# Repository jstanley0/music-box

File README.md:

# music-box
Chiptune music player featuring SN76489 and ATtiny861/ATtiny84

## Overview
This project grew out of a Wikipedia surfing session. In reading about the computers of my childhood,
I came across an article about the TI SN76489 sound chip, used by two of the machines I used as a kid
(the TI 99/4A and IBM PCjr). I wondered if you can readily buy this IC, and if you can talk to it
reasonably easily with modern hardware. The answer to both questions is yes!

## How it works
All eight pins of PORTA are connected to the SN76489's data lines. PB4 connects to /WE and latches
a value to the chip. PB5 (CLKO) outputs the ATtiny861's clock signal directly to the sound chip's
clock input. /OE is permanently tied low and READY is ignored. I'm not sharing a bus with anything 
else...

The MCU firmware plays music from an array of bytes stored in program memory (in songs.c). It's a
very simple binary format with three one-byte commands that play a note, play a noise, and sleep.
To keep things simple, I ignore note-off events and simply make each note decay at a constant
linear rate after it is struck. Much like an actual music box!

## Loading music
util/process_midi_file.cpp will take a MIDI file and output a set of arrays for songs.c. It makes
use of [light-midi-parser](https://github.com/imhcyx/light-midi-parser) as a submodule.

## ATtiny84
This project can also be built for the ATtiny84, via `make -e DEVICE=attiny84`.
With this target there will be just one blinking light, rather than one per channel. See main.c for wiring differences.

## See also
I've also created a more elaborate stereo two-chip player using the Raspberry Pi Pico, [pico-player](https://github.com/jstanley0/pico-player).

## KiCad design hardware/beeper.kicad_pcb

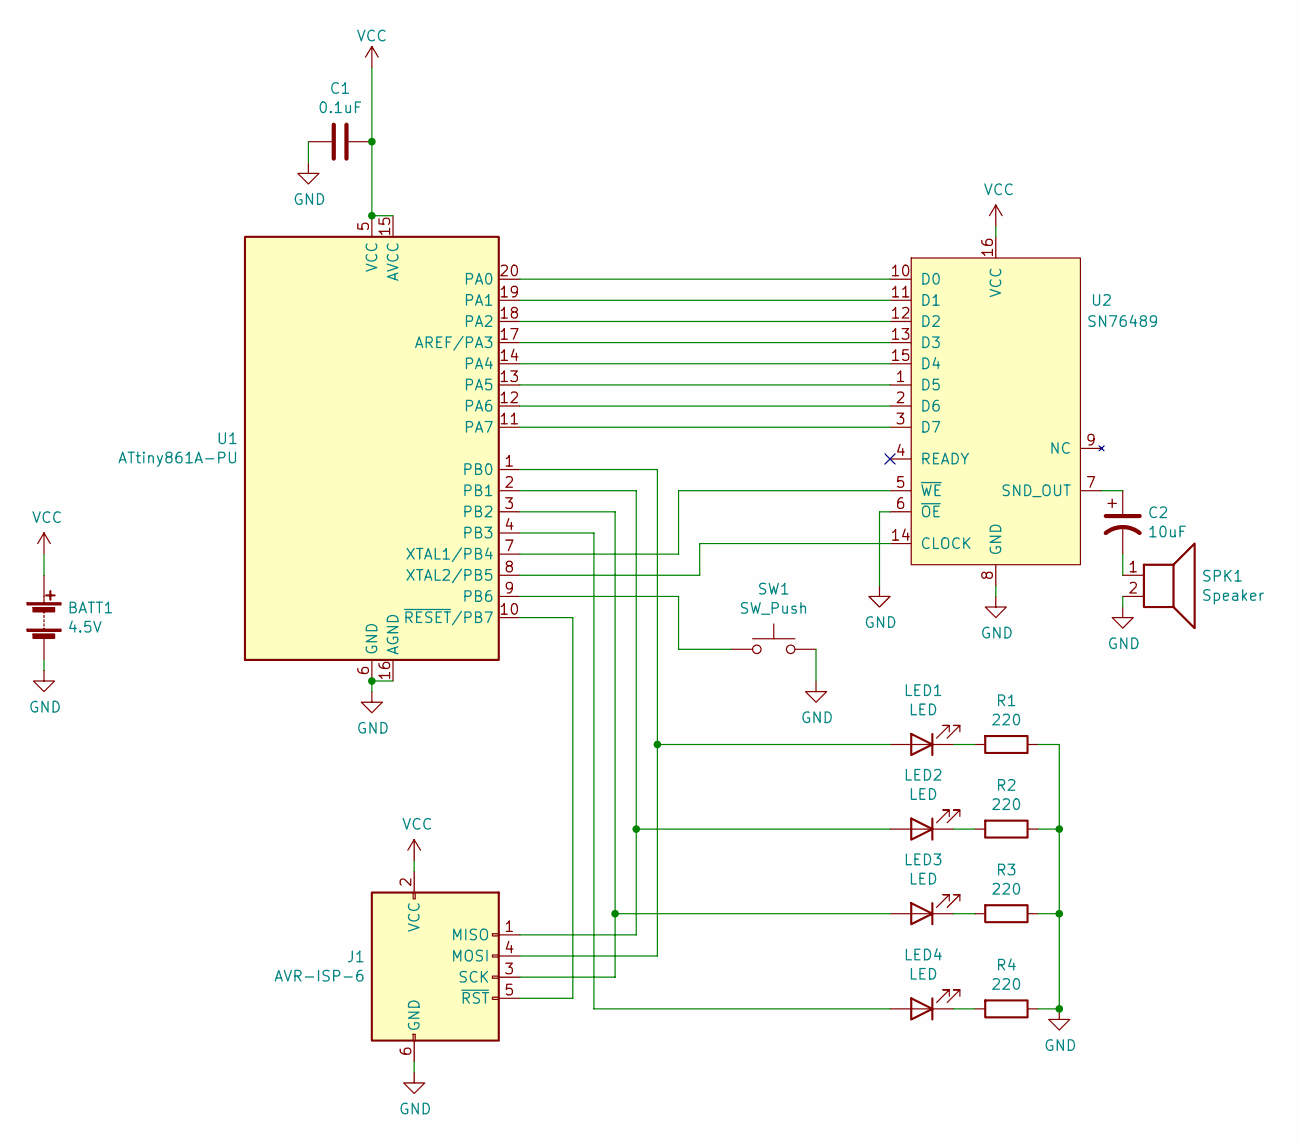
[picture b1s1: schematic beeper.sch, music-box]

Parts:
BATT1: 4.5V; PinHeader_1x02_P2.54mm_Vertical
C1: 0.1uF; C_Disc_D3.0mm_W1.6mm_P2.50mm
C2: 10uF; CP_Radial_D6.3mm_P2.50mm
J1: AVR-ISP-6; PinHeader_2x03_P2.54mm_Vertical
LED1, LED2, LED3, LED4: LED; LED_D5.0mm_Clear
R1, R2, R3, R4: 220; R_Axial_DIN0204_L3.6mm_D1.6mm_P1.90mm_Vertical
SPK1: Speaker; PinHeader_1x02_P2.54mm_Vertical
SW1: SW_Push; SW_Tactile_Straight_KSA0Axx1LFTR
U1: ATtiny861A-PU; DIP-20_W7.62mm
U2: SN76489; DIP-16_W7.62mm

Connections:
GND: BATT1.2 (-), C1.2, J1.6 (GND), R1.1, R2.1, R3.1, R4.1, SPK1.2, SW1.2, U1.6 (GND), U1.16 (AGND), U2.6 (~OE), U2.8 (GND)
unnamed: C2.1, U2.7 (SND_OUT)
unnamed: C2.2, SPK1.1
unnamed: J1.1 (MISO), LED2.2 (A), U1.2 (PB1)
unnamed: J1.3 (SCK), LED3.2 (A), U1.3 (PB2)
unnamed: J1.4 (MOSI), LED1.2 (A), U1.1 (PB0)
unnamed: J1.5 (~RST), U1.10 (~RESET~/PB7)
unnamed: LED1.1 (K), R1.2
unnamed: LED2.1 (K), R2.2
unnamed: LED3.1 (K), R3.2
unnamed: LED4.1 (K), R4.2
unnamed: LED4.2 (A), U1.4 (PB3)
unnamed: SW1.1, U1.9 (PB6)
unnamed: U1.7 (XTAL1/PB4), U2.5 (~WE)
unnamed: U1.8 (XTAL2/PB5), U2.14 (CLOCK)
unnamed: U1.11 (PA7), U2.3 (D7)
unnamed: U1.12 (PA6), U2.2 (D6)
unnamed: U1.13 (PA5), U2.1 (D5)
unnamed: U1.14 (PA4), U2.15 (D4)
unnamed: U1.17 (AREF/PA3), U2.13 (D3)
unnamed: U1.18 (PA2), U2.12 (D2)
unnamed: U1.19 (PA1), U2.11 (D1)
unnamed: U1.20 (PA0), U2.10 (D0)
VCC: BATT1.1 (+), C1.1, J1.2 (VCC), U1.5 (VCC), U1.15 (AVCC), U2.16 (VCC)

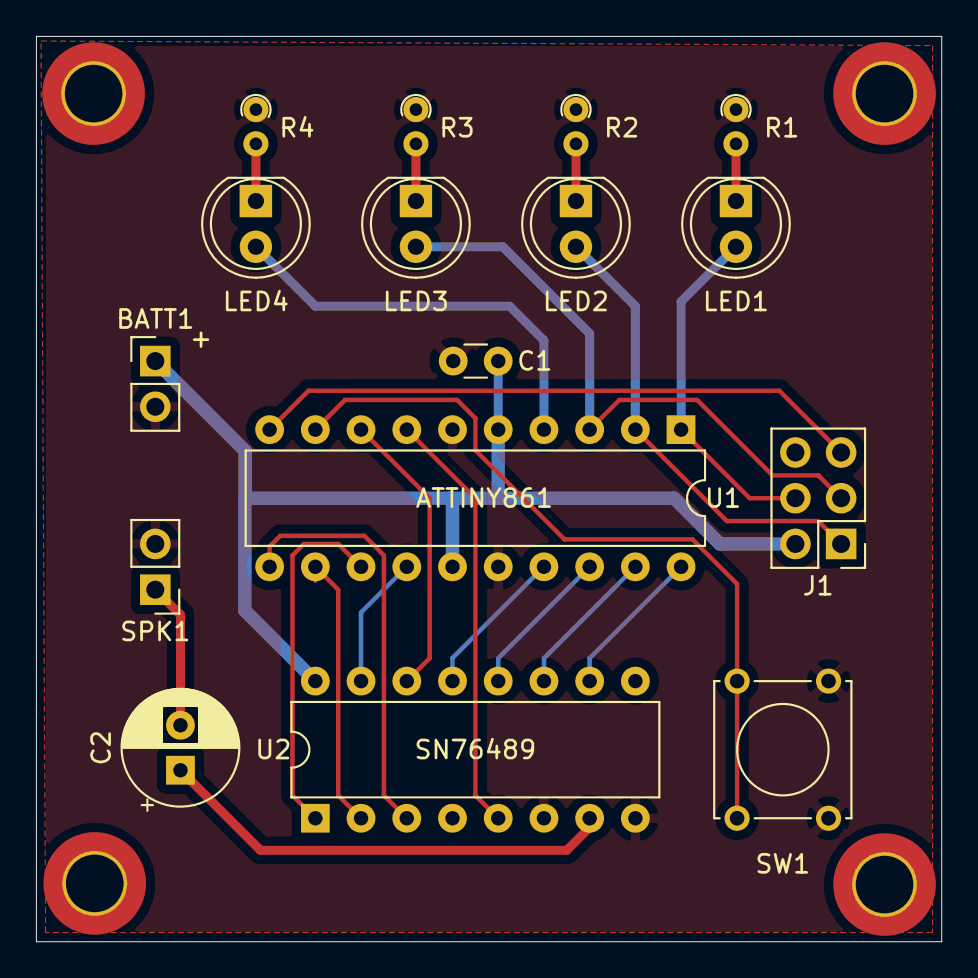
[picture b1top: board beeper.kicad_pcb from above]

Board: 2 copper layers, 50.3 x 50.3 mm, 17 parts (0 on the bottom side), 24 nets.

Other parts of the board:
\: MountingHole_3.2mm_M3_ISO7380_Pad_TopBottom

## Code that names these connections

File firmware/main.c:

// attiny861 / TI SN76489 music box
// (c) 2021 by Jeremy Stanley

// port assignments (ATtiny861 -> TI SN76489):
// PA0..PA7 -> D7..D0
// PB4 -> /WE
// PB5 -> CLOCK (via CKOUT fuse)

// other pin assignments:
// PB0..3 -> blinkenlights
// PB6 -> tac switch

// alternatively this can be compiled for ATtiny84
// using `make -e DEVICE=attiny84`
// which uses the following port assignments:
// PA0..PA7 -> D7..D0
// PB1 -> /WE
// PB2 -> CLOCK
// PB0 -> blinkenlight (just one)

#include <avr/io.h>
#include <avr/pgmspace.h>
#include <avr/sleep.h>
#include <avr/interrupt.h>
#include <util/delay.h>

#include "songs.h"
const uint8_t *const songs[] PROGMEM = { st_elsewhere, lament, macgyver, brooklet, quantum_leap, nervous, hogans_heroes, charlie_brown };
const uint8_t NUM_SONGS = sizeof(songs) / sizeof(songs[0]);

#ifdef __AVR_ATtiny84__
#define WE_BIT PORTB1
#else
#define WE_BIT PORTB4
#endif

// hi-hat, ride cymbal, etc. don't play at full volume
#define ATTENUATED_PERCUSSION_LEVEL 4

void init_clock()
{
  // change clock divider from /8 to /4 so we run at 2MHz,
  // which is an acceptable clock frequency for the SN76489
  // (at 4MHz, we lose too much low range, and at 1MHz, high notes get out of tune)
  CLKPR = (1 << CLKPCE);  // Clock Prescaler Change Enable - this part is necessary
  CLKPR = (1 << CLKPS1);  // 4x divider
}

void init_io()
{
  DDRA  = 0xff;
#ifdef __AVR_ATtiny84__
  DDRB  = 0b00000111;
  PORTB = (1 << WE_BIT);
#else
  DDRB  = 0b00111111;
  PORTB = (1 << PORTB6) | (1 << WE_BIT);
#endif
}

void send_byte(uint8_t byte)
{
  PORTA = byte;
  PORTB &= ~(1 << WE_BIT);
  _delay_us(16);  // 32 clock cycles at 2MHz
  PORTB |= (1 << WE_BIT);
}

void send_frequency(uint8_t voice, uint16_t freq)
{
  send_byte(0x80U | (voice << 5) | (freq & 0x0F));
  send_byte(freq >> 4);
}

void send_noise(uint8_t n)
{
  send_byte(0xE0U | n);
}

void send_attenuation(uint8_t voice, uint8_t atten)
{
  send_byte(0x90U | (voice << 5) | atten);
}

uint8_t playing_atten[4] = { 15, 15, 15, 15 };

#ifdef __AVR_ATtiny84__
volatile uint8_t OCR0A_buf = 0;

void update_blinkenlight()
{
  uint8_t blinkenlight = 0;
  for(uint8_t i = 0; i < 4; ++i) {
    blinkenlight += (63 >> playing_atten[i]);
  }
  OCR0A_buf = blinkenlight;
}
#else
static const uint8_t fade_table[16] PROGMEM = {254, 179, 125, 88, 61, 43, 30, 21, 15, 10, 7, 5, 4, 2, 1, 0};

volatile uint8_t OCR0A_buf = 0, OCR0B_buf = 0;
void set_led(uint8_t voice, uint8_t atten)
{
    static volatile uint8_t *intensity_reg[4] = { &OCR0A_buf, &OCR1A, &OCR0B_buf, &OCR1B };
    *intensity_reg[voice] = pgm_read_byte(&fade_table[playing_atten[voice]]);
}
#endif

void note(uint8_t note)
{
  // pick the quietest voice
  uint8_t v = 0;
  for(uint8_t i = 1; i < 3; ++i) {
    if (playing_atten[i] > playing_atten[v])
      v = i;
  }

  // play the note!
  playing_atten[v] = 0;
  send_frequency(v, pgm_read_word(&note_table[note]));
  send_attenuation(v, 0);
#ifndef __AVR_ATtiny84__
  set_led(v, 0);
#endif
}

void noise(uint8_t n, uint8_t initial_attenuation)
{
  playing_atten[3] = initial_attenuation;
  send_noise(n);
  send_attenuation(3, initial_attenuation);
#ifndef __AVR_ATtiny84__
  set_led(3, 0);
#endif
}

void decay()
{
  for(uint8_t i = 0; i < 3; ++i) {
    if (playing_atten[i] < 15) {
      send_attenuation(i, ++playing_atten[i]);
#ifndef __AVR_ATtiny84__
      set_led(i, playing_atten[i]);
#endif
    }
  }
}

void decay_noise()
{
  if (playing_atten[3] < 15) {
    send_attenuation(3, ++playing_atten[3]);
#ifndef __AVR_ATtiny84__
    set_led(3, playing_atten[3]);
#endif
  }
}

void silence()
{
  for(int i = 0; i < 4; ++i)
    send_attenuation(i, 15);
}

volatile uint8_t g_Tick = 0;

#ifdef __AVR_ATtiny84__

ISR(TIM0_COMPA_vect)
{
  // LED off
  PORTB &= 0b11111110;
}

ISR(TIM0_OVF_vect)
{
  // LED on, maybe
  OCR0A = OCR0A_buf;
  if (OCR0A_buf > 0)
    PORTB |= 1;

  // music heartbeat
  g_Tick += 1;
}

#else

// LED 1 off
ISR(TIMER0_COMPA_vect)
{
  PORTB &= 0b11111110;
}

// LED 3 off
ISR(TIMER0_COMPB_vect)
{
  PORTB &= 0b11111011;
}

ISR(TIMER0_OVF_vect)
{
  // LED 1 on, maybe
  OCR0A = OCR0A_buf;
  if (OCR0A_buf > 0)
    PORTB |= 0b001;

  // LED 3
  OCR0B = OCR0B_buf;
  if (OCR0B_buf > 0)
    PORTB |= 0b100;

  // music heartbeat
  g_Tick += 1;
}

#endif

void sleep_one_tick()
{
  while (g_Tick == 0) {
    set_sleep_mode(SLEEP_MODE_IDLE);
    sleep_enable();
    sleep_cpu();
  }
  g_Tick -= 1;
}

void init_interrupts()
{
#ifdef __AVR_ATtiny84__
  // one LED with software PWM
  TCCR0A = 0;                            // normal mode, 8-bit
  TCCR0B = (1 << CS01) | (1 << CS00);    // 1/64 prescaler
  TIMSK0 = (1 << OCIE0A) | (1 << TOIE0); // enable COMPA and OVF vectors
#else
  // this is gonna be a bit hacky because THERE ARE FOUR LIGHTS.

  // two of them (LEDs 2 and 4) are easy: they're on OC1A and OC1B pins, so we can use fast PWM mode
  TCCR1A = (1 << COM1A1) | (1 << COM1B1) | (1 << PWM1A) | (1 << PWM1B);
  // set prescaler 1/64: 2MHz / 256 / 64 = 122Hz, a perfectly cromulent refresh rate
  TCCR1B = (1 << CS12) | (1 << CS11) | (1 << CS10);

  // we can't use the third PWM channel (because its pin is shared with CLKO)
  // and there is no fourth PWM channel anyway
  // so we'll use timer0 for LEDs 1 and 3
  TCCR0A = 0;                            // normal mode, 8-bit
  TCCR0B = (1 << CS01) | (1 << CS00);    // 1/64 prescaler
  TIMSK |= (1 << OCIE0A) | (1 << OCIE0B) | (1 << TOIE0); // enable COMPA, COMPB, and overflow vectors
#endif
}

void play_song(uint8_t song_num)
{
  const uint8_t *PROGMEM song_data = (uint8_t *)pgm_read_word(&songs[song_num]);
  uint16_t song_pos = 0;
  uint8_t wait_cycles = 50;
  uint8_t decay_cycles = 0;
  uint8_t noise_cycles = 0;
  int8_t noise_target = 0;
  int8_t fade_out = 0;

  for(;;)
  {
    sleep_one_tick();

#ifdef __AVR_ATtiny84__
    update_blinkenlight();
#else
    if (0 == (PINB & (1 << PB6))) {
        fade_out = 100;
    }
#endif

    if (++decay_cycles == 6) {
      decay_cycles = 0;
      decay();
    }
    if (++noise_cycles == noise_target) {
      noise_cycles = 0;
      decay_noise();
    }

    if (fade_out > 0) {
        if (--fade_out == 0)
            break;
        else
            continue;
    }

    if (wait_cycles > 0) {
      --wait_cycles;
      continue;
    }

    // keep executing song commands until we hit a delay or end of song
    while(wait_cycles == 0) {
      uint8_t song_cmd = pgm_read_byte(&song_data[song_pos]);
      uint8_t noise_atten;
      switch(song_cmd & 0xC0) {
      case 0: // note
        note(song_cmd);
        break;
      case 0x40: // delay
        wait_cycles = song_cmd & 0x3F;
        break;
      case 0x80: // noise
        //  7  6  5  4  3  2  1  0
        //  1  0 A0 S1 S0 N2 N1 N0
        noise_target = 1 + ((song_cmd & 0x18) >> 3);
        noise_atten = (song_cmd & 0x20);
        noise_cycles = 0;
        noise(song_cmd & 0x07, noise_atten ? ATTENUATED_PERCUSSION_LEVEL : 0);
        break;
      case 0xC0: // end song
        fade_out = 100;
      }
      ++song_pos;
    }
  }
}

int main(void)
{
  init_clock();
  init_io();
  silence();
  init_interrupts();
  sei();

  uint8_t song_num = 0;
  for(;;) {
    play_song(song_num);
    if (++song_num >= NUM_SONGS)
        song_num = 0;
  }
}

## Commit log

2021-01-24 initial commit for AVR music box
2021-01-25 ADSR envelope, MIDI parser, blinkenlight
2021-01-25 on second thought, I don't think this is necessary
    we may spend upwards of 100us talking to the sound chip but that
    isn't long enough to cause noticeable glitches in the blinkenlight
2021-01-25 reorg
2021-01-25 delay for half a second before starting
    to avoid stuttering as the power switch is engaged
2021-01-26 old debugging cruft
2021-01-26 simplify
    you know what music boxes don't have? note-off events.
    let's get rid of those. this vastly simplifies squashing a song
    down to 3 channels, plus it cuts storage requirements almost
    in half!
    all notes will attenuate until they're gone, and when we start a
    new note, we will pick the channel that's quietest
2021-01-26 fix delay logic
2021-01-26 quantize on absolute time
2021-01-26 coalesce adjacent delays
    (there are midi events between these delays, but not midi events
    we pay attention to)
2021-01-26 add percussion on noise channel
    noise decays faster than notes, and actually doesn't sound
    too bad
    the mapping in the midi processor needs some experimentation,
    clearly
2021-01-26 flesh out percussion a bit
    also, with percussion in the mix, the blinkenlight PWM was
    glitching. ISR_NOBLOCK fixes it
2021-01-26 percussion dynamics
    since we have some unused bits, might as well allow stuff like
    - hi-hat being quieter than other percussion
    - cymbals and open hi-hat decaying more slowly than other percussion
2021-02-02 make ispcheck: quick comm check with the micro
2021-02-14 round, rather than truncate, frequency table values
    high notes got noticeably sharp
2021-02-15 fix attenuated percussion
2021-02-15 schematic and PCB
    ... for a slightly different project (using ATTiny861 and *four*
    blinkenlights). I haven't updated the firmware to match this yet.
    but I have sent out for PCB manufacture...
2021-02-19 shorter traces
2021-03-13 beginnings of ATtiny861 port
    it's functional, but I haven't implemented the per-voice
    blinkenlight PWM yet - they're all just flashing in unison
    naturally, there are three timer0 compare-match vectors,
    A, B, and D. there's a C register but no interrupt :|
    ... so I'll come up with something
2021-03-14 THERE ARE FOUR LIGHTS
    as part of the deal, I needed to change the player tick time
    so we can get it with a timer overflow. now instead of 10ms,
    it is 8.192ms. songs previously converted will play fast.
    also, both timers are doing LED PWM. song playing is moved
    out of the interrupt handler, which it never should have been in
    to begin with. I've tried to deal with the player code getting
2021-03-14 update LED PWM only when it changes
2021-03-14 don't attenuate percussion _that_ much
    also sustain melodic notes longer to compensate for the faster
    timer-overflow heartbeat
2021-03-18 fix LED PWM glitch
    by double-buffering OCR0x changes
    also use a lookup table rather than a bit shift
2021-03-18 update LED intensity immediately
    if we wait until decay begins, we never even use the highest
    brightness setting
2021-04-01 add video
2021-04-01 missed this comment
2021-04-08 re-add ATtiny84 support
    this preserves a few bug fixes made since the ATtiny861 port
    compile with `make -e DEVICE=attiny84`
    be sure to `make clean` if you've already built the ATtiny861 binary
    because it will definitely not work on the ATtiny84
2021-05-11 add transpose option
2021-05-15 multiple songs
